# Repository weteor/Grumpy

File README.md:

### grumpy

28 key (3-row) angled unibody keyboard with col stagger 

## Features

###### MX Xiao-Version:

- spacing: MX
- case: open bottom (3dp)
- Hotswap sockets (MX)
- Seeed Xiao Controller
  - RP2040 (w/ QMK, Vial)
  - BLE (w/ZMK)
  - SAMD21 (should work, don't have one to test)
- gerber and case files are supplied (kicad files, stl as well as cadquery files)
- completely open source, permissive license ([CERN-OHL-P](https://cern-ohl.web.cern.ch/home))

###### MX/ChocV2 CH552T-Version:

- spacing: MX
- case: top w/ bottom plate (top and bottom 3dp)
- Hotswap sockets (MX and Choc V1/V2)
- CH552T Controller (w/ FAK firmware)
- gerber and case files are supplied (kicad files, stl as well as cadquery files)
- completely open source, permissive license ([CERN-OHL-P](https://cern-ohl.web.cern.ch/home))

###### ChocV1 Xiao-Version:

- spacing: choc
- case: top w/ bottom plate (top 3dp/cnc, bottom 3dp)
- Hotswap sockets (Choc V1)
- Seeed Xiao Controller
  - RP2040 (w/ QMK, Vial)
  - BLE (w/ZMK)
  - SAMD21 (should work, don't have one to test)
- gerber and case files are supplied (kicad files, stl as well as cadquery files)
- completely open source, permissive license ([CERN-OHL-P](https://cern-ohl.web.cern.ch/home))

## Want one?

All production files you need to build your own board can be found [here](./prod/).

The case has no bottom and ends right below the HS Sockets. You may either use it as is, but preferably use some 2-3mm self-adhesive neopren on the whole pcb. The case will be hard to print on a FDM Printer, so maybe use a service to print it in resin or nylon.

Apart from the pcb and optionally a case you need:

###### Xiao-Version

- 28 hotswap sockets
- 28 diodes (1N4148 int SOT-123)
- 28 of your favourite switches
- 1 Controller

###### CH552T-Version:

- 28 hotswap sockets
- 28 diodes (1N4148 int SOT-123)
- 28 of your favourite switches
- 1x CH552T (TSSOP-20)
- 1x USBLC6-2SC6 (SOT-23-6)
- 1x 10kOhm resistor (SMD 0603)
- 2x 5.1kOhm resistors (SMD 0603)
- 2x 100nF capacitors (SMD 0603)
- 1x USB Connector C-Type, 12 pin/16pin, mid-mount (1.6mm)

### firmware

###### Xiao-Version:

firmware configs for qmk and vial can be found in the [firmware folder](./firmware).

The first time the pcb is plugged in, the bootloader will provide a drive to upload the firmware file. 

###### CH552T-Version:

firmware config for FAK can be found [here](https://github.com/weteor/fak-config/tree/main/keyboards/grumpy). Please also see [FAK-Firmware site](https://github.com/semickolon/fak) for more information

Bootloader should be available on first plugins until firmware is written. After that either use the firmware BOOT to go into bootloader, or hold the boot button on the pcb pressed while pluggin in the usb cable.

## the rest

Everything in this repository is free to use however you might see fit. If you want to support me and my projects, please consider linking back to this repository if you build/change/use anything.

If you would like to send me a tip, you could do it [here](https://ko-fi.com/weteor) (Please don't feel like you have to).

## more pictures

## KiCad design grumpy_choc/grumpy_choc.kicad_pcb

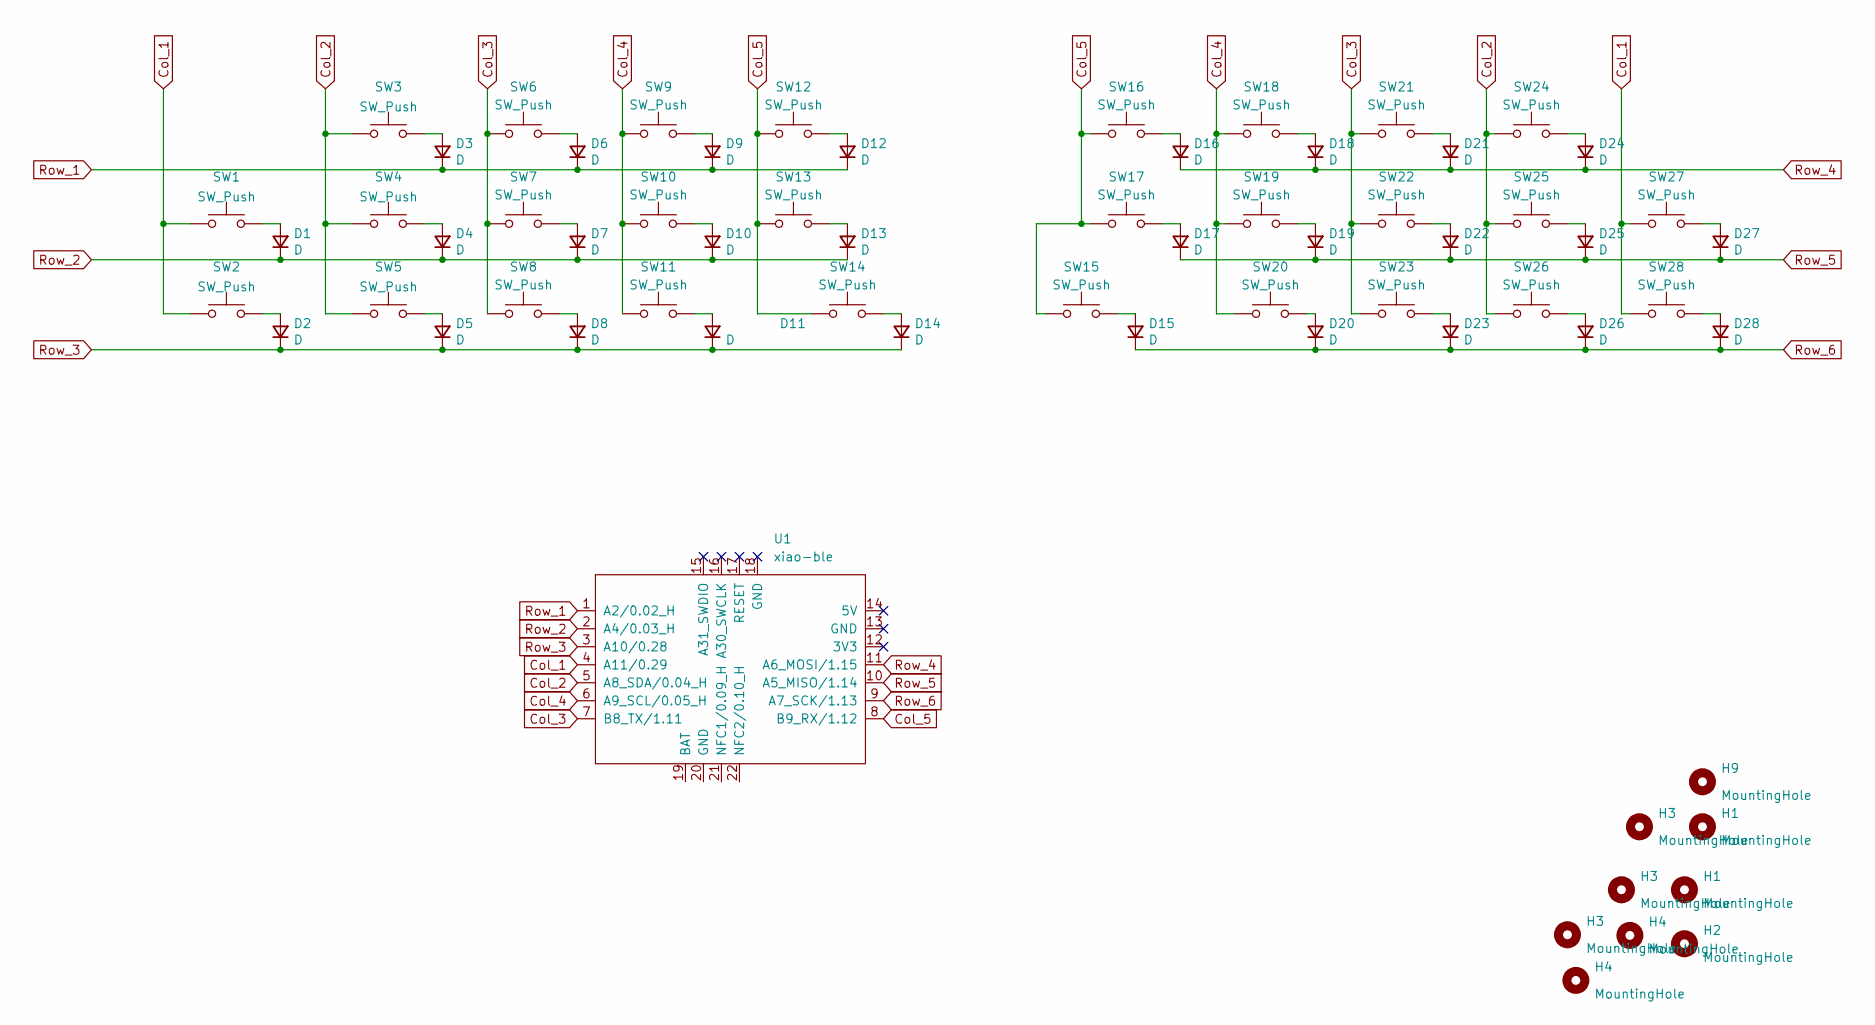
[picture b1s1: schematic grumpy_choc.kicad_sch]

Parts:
D1, D2, D3, D4, D5, D6, D7, D8, D9, D10, D11, D12, D13, D14, D15, D16, D17, D18, D19, D20, D21, D22, D23, D24, D25, D26, D27, D28: D; D_SOD-123
H1, H2, H3, H4, H9: MountingHole; MountingHole_4mm
SW1, SW2, SW3, SW4, SW5, SW6, SW7, SW8, SW9, SW10, SW11, SW12, SW13, SW16, SW17, SW18, SW19, SW20, SW21, SW22, SW23, SW24, SW25, SW26, SW27, SW28: SW_Push; ChocV1_V2_Hotswap
SW14, SW15: SW_Push; ChocV1_V2_Hotswap_1.5u
U1: xiao-ble; xiao-ble-smd_upside_down_npads

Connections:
Col_1: SW1.1, SW2.1, SW27.1, SW28.1, U1.4 (A11/0.29)
Col_2: SW3.1, SW4.1, SW5.1, SW24.1, SW25.1, SW26.1, U1.5 (A8_SDA/0.04_H)
Col_3: SW6.1, SW7.1, SW8.1, SW21.1, SW22.1, SW23.1, U1.7 (B8_TX/1.11)
Col_4: SW9.1, SW10.1, SW11.1, SW18.1, SW19.1, SW20.1, U1.6 (A9_SCL/0.05_H)
Col_5: SW12.1, SW13.1, SW14.1, SW15.1, SW16.1, SW17.1, U1.8 (B9_RX/1.12)
unnamed: D1.2 (A), SW1.2
unnamed: D2.2 (A), SW2.2
unnamed: D3.2 (A), SW3.2
unnamed: D4.2 (A), SW4.2
unnamed: D5.2 (A), SW5.2
unnamed: D6.2 (A), SW6.2
unnamed: D7.2 (A), SW7.2
unnamed: D8.2 (A), SW8.2
unnamed: D9.2 (A), SW9.2
unnamed: D10.2 (A), SW10.2
unnamed: D11.2 (A), SW11.2
unnamed: D12.2 (A), SW12.2
unnamed: D13.2 (A), SW13.2
unnamed: D14.2 (A), SW14.2
unnamed: D15.2 (A), SW15.2
unnamed: D16.2 (A), SW16.2
unnamed: D17.2 (A), SW17.2
unnamed: D18.2 (A), SW18.2
unnamed: D19.2 (A), SW19.2
unnamed: D20.2 (A), SW20.2
unnamed: D21.2 (A), SW21.2
unnamed: D22.2 (A), SW22.2
unnamed: D23.2 (A), SW23.2
unnamed: D24.2 (A), SW24.2
unnamed: D25.2 (A), SW25.2
unnamed: D26.2 (A), SW26.2
unnamed: D27.2 (A), SW27.2
unnamed: D28.2 (A), SW28.2
Row_1: D3.1 (K), D6.1 (K), D9.1 (K), D12.1 (K), U1.1 (A2/0.02_H)
Row_2: D1.1 (K), D4.1 (K), D7.1 (K), D10.1 (K), D13.1 (K), U1.2 (A4/0.03_H)
Row_3: D2.1 (K), D5.1 (K), D8.1 (K), D11.1 (K), D14.1 (K), U1.3 (A10/0.28)
Row_4: D16.1 (K), D18.1 (K), D21.1 (K), D24.1 (K), U1.11 (A6_MOSI/1.15)
Row_5: D17.1 (K), D19.1 (K), D22.1 (K), D25.1 (K), D27.1 (K), U1.10 (A5_MISO/1.14)
Row_6: D15.1 (K), D20.1 (K), D23.1 (K), D26.1 (K), D28.1 (K), U1.9 (A7_SCK/1.13)

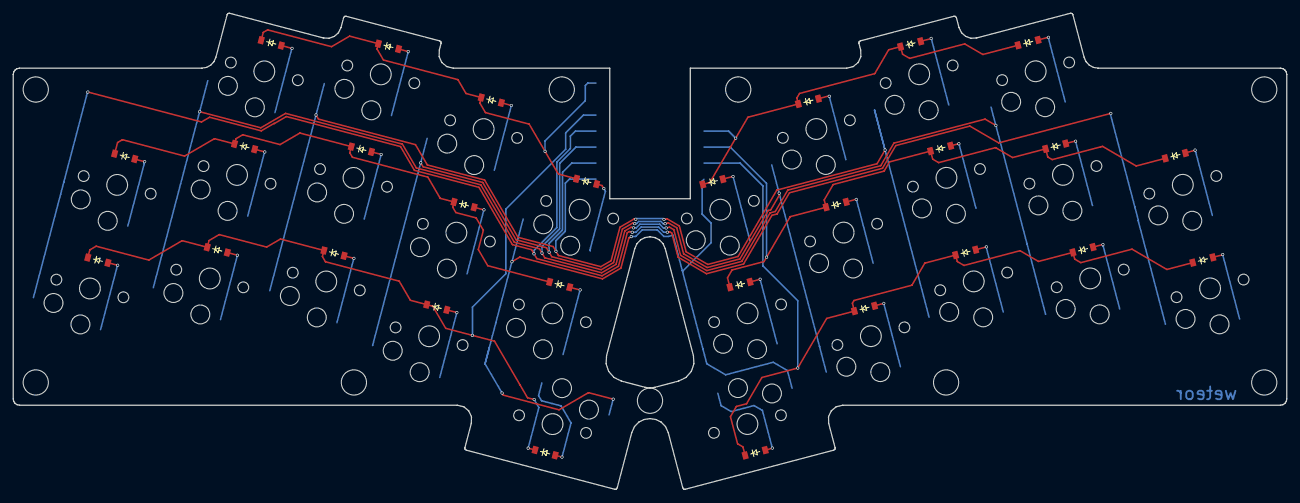
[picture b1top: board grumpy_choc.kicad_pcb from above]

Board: 2 copper layers, 202.2 x 75.6 mm, 66 parts (1 on the bottom side), 39 nets.

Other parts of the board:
H5, H6, H7, H8: MountingHole; MountingHole_4mm

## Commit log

2023-08-01 pcb cad data
2023-08-01 case cad files
2023-08-01 add production data
2023-08-01 add firmware files
2023-08-01 add images
2023-08-01 add readme and license
2023-08-01 fix readme
2023-08-02 clean up case file
2024-01-01 fix vial build
2024-02-25 add: test rewrite of casefile in build123d
2024-06-19 add version with ch552t MCU and combined Choc V1, V2 and MX Footprints
2024-06-19 add case for choc builds
2024-06-19 add wip mx case with plate and bottom
2024-07-09 add gerbers
2024-07-09 add image
2025-01-21 add choc-spaced Version
